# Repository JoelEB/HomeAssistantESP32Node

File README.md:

# HomeAssistantESP32Node
ESP32Node for Home Assitant

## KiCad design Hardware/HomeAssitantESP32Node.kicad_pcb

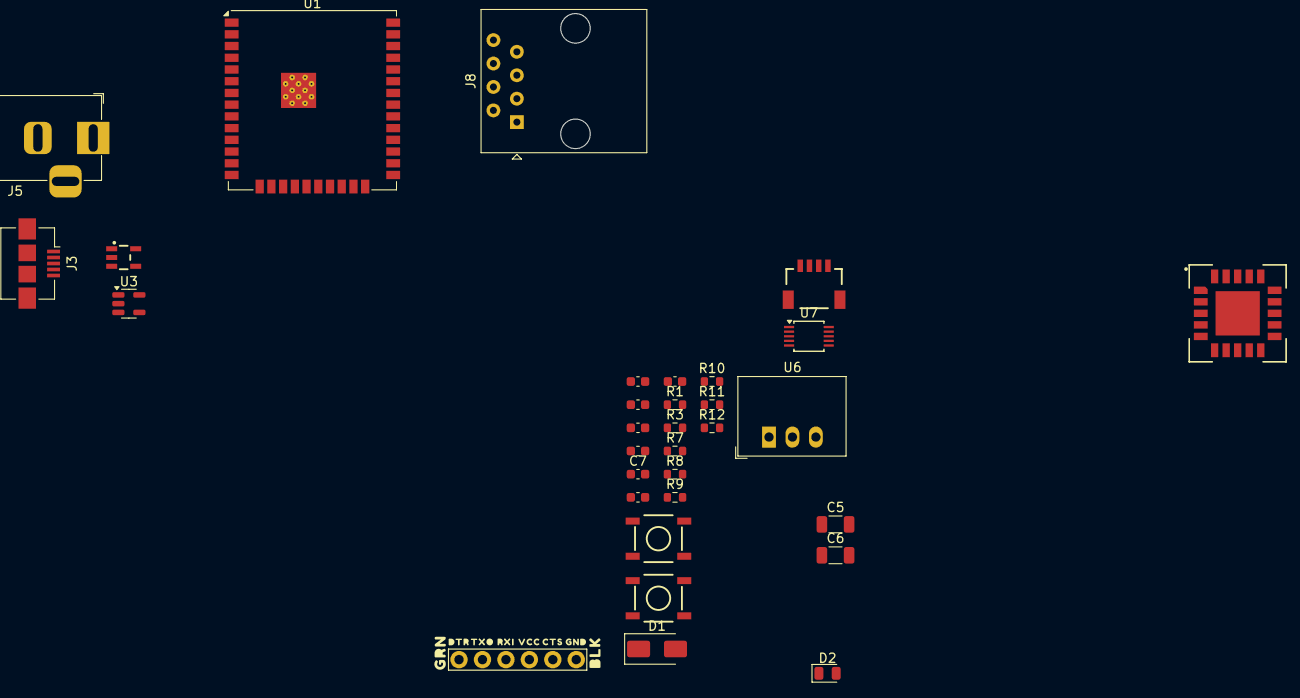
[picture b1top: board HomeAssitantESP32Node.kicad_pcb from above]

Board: 2 copper layers, 32 parts (0 on the bottom side), 14 nets, no tracks yet.

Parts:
C1, C2: 1uF; C_0603_1608Metric
C3, C4: 10uF; C_0603_1608Metric
C5, C6: 10UF; C_1206_3216Metric
C7, C8: 0.1uF; C_0603_1608Metric
C9: 4.7uF; C_0603_1608Metric
D1: DIODE; D_SMA
D2: LED; LED_0805_2012Metric
J1: Qwiic_RA; JST_SMD_1.0mm-4_RA
J2: Conn_01x06; 6_Pin_Serial_Target_Side
J3: USB_B_Micro; USB_Micro-B_Amphenol_10104110_Horizontal
J5: Barrel_Jack_Switch; BarrelJack_Horizontal
J8: RJ45; RJ45_Amphenol_54602-x08_Horizontal
R1: 10K; R_0603_1608Metric
R3: 330; R_0603_1608Metric
R7, R9, R10, R12: 390; R_0603_1608Metric
R8, R11: 100; R_0603_1608Metric
SW1, SW2: SMD_5.2x5.2mm_h2.5mm; Momentary_SMD_5.2x5.2mm_h2.5mm
U1: ESP32-WROOM-32UE
U2: AP2112K-3.3; SOT23-5
U3: XC6220B331MR; SOT-23-5
U4: SCD41; SCD4X
U6: R-78E5.0-0.5; Converter_DCDC_RECOM_R-78E-0.5_THT
U7: PCA9615; TSSOP-10_3x3mm_P0.5mm

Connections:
0: SW1.2 (B), U1.25 (IO0)
+5V: C6.1, C7.1, R3.1, R7.1, R10.1, U7.1 (VDDA), U7.10 (VDDB)
D_SCL+: J8.5, R7.2, R8.1, U7.7 (D_SCL+)
D_SCL-: J8.4, R8.2, R9.1, U7.6 (D_SCL-)
D_SDA+: J8.7, R10.2, R11.1, U7.8 (D_SDA+)
D_SDA-: J8.8, R11.2, R12.1, U7.9 (D_SDA-)
GND: C1.2, C2.2, C3.2, C4.2, C5.2, C6.2, C7.2, C8.2, C9.2, D2.1 (K), J1.1, J2.1, J3.5 (GND), J5.2, J5.3, J8.1, R9.2, R12.2, SW1.1 (A), SW2.1 (A), U1.1 (GND), U1.15 (GND), U1.38 (GND), U1.39 (GND), U2.2 (GND), U3.2 (GND), U4.6 (GND), U4.20 (GND), U4.21 (GND), U7.5 (GND)
unnamed: D2.2 (A), R3.2
PULL_UP: C2.1, C4.1, C8.1, C9.1, J1.2, J2.3, R1.1, R1.2, SW2.2 (B), U1.2 (3V3), U1.3 (EN), U2.5 (VOUT), U3.5 (VOUT), U4.7 (VDD), U4.19 (VDDH)
RX: J2.4, U1.35 (TXD0/IO1)
SCL: J1.4, U1.36 (IO22), U4.9 (SCL)
SDA: J1.3, U1.37 (SDO_V/IO23), U4.10 (SDA)
TX: J2.5, U1.34 (RXD0/IO3)
VIN: C1.1, C3.1, J3.1 (VBUS), J5.1, U2.1 (VIN), U2.3 (EN), U3.1 (VIN), U3.3 (CE)

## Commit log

2024-07-24 Adding KiCad Files
